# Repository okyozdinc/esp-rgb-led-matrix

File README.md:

# PIXELIX <!-- omit in toc -->

Full RGB LED matrix, based on an ESP32 and WS2812B LEDs.

- [Motivation](#motivation)
- [Overview](#overview)
  - [Original setup](#original-setup)
  - [Others](#others)
- [Installation](#installation)
- [Very First Startup](#very-first-startup)
  - [Variant 1: Configure wifi station SSID and passphrase with the browser](#variant-1-configure-wifi-station-ssid-and-passphrase-with-the-browser)
  - [Variant 2: Configure wifi station SSID and passphrase with the terminal](#variant-2-configure-wifi-station-ssid-and-passphrase-with-the-terminal)
  - [Pixelix Is Ready](#pixelix-is-ready)
- [User Interface](#user-interface)
- [Documentation](#documentation)
- [Used Libraries](#used-libraries)
- [FAQ](#faq)
  - [Where to change panel topology of the LED matrix?](#where-to-change-panel-topology-of-the-led-matrix)
  - [How to change text properties?](#how-to-change-text-properties)
  - [The display only shows a error code, like "E4". What does that mean?](#the-display-only-shows-a-error-code-like-e4-what-does-that-mean)
  - [How can I use animated icons?](#how-can-i-use-animated-icons)
  - [How do I know that my sensor is recognized?](#how-do-i-know-that-my-sensor-is-recognized)
  - [Why do I see sometimes values from the LDR in the SensorPlugin, although no LDR is installed?](#why-do-i-see-sometimes-values-from-the-ldr-in-the-sensorplugin-although-no-ldr-is-installed)
  - [How can I use alternative icons?](#how-can-i-use-alternative-icons)
  - [Is it possible to use a font with 8px height?](#is-it-possible-to-use-a-font-with-8px-height)
  - [How to configure the date/time format?](#how-to-configure-the-datetime-format)
- [Issues, Ideas And Bugs](#issues-ideas-and-bugs)
- [License](#license)
- [Contribution](#contribution)

# Motivation
I want to have a remote display to show multiple kind of information, running 24/7 reliable. Connected over wifi to the local network, it can be controlled via REST API or websocket.

| Some impressions |   |
| - | - |
|  |  |
|  |  |
|  | ... |

# Overview

The firmware contains a plugin concept (at compile time) to provide different functionalities. Each plugin can create its own layout and place the information as required. If you are only interested in showing just text provided via REST API, choose the JustTextPlugin. It uses the whole display size and will scroll text automatically. Sometimes in front of the text a nice icon is required, in this case choose the IconTextPlugin. These are only examples and you will find more in the [plugin list](./doc/PLUGINS.md).

A little bit more detail about the generic plugins and the first idea can be found in this [rough overview](./doc/Overview.pdf).

## Original setup
The original setup during development and the first release was:
* [ESP32 DevKitV1](https://github.com/playelek/pinout-doit-32devkitv1)
* WS2812B 5050 8x32 RGB Flexible LED Matrix Panel
* Power supply 5 V / 4 A

The following shows the absolute minimal wiring setup:

> :warning: **If you power all via USB**: Be very careful, because it may destroy your esp32 board if the LED current gets too high. Avoid increasing the LED display brightness or filling it complete with white pixels. Please use a external power supply with at least 5V / 4A.

## Others

In the meantime several other boards are supported as well. You can see them in the platformio configuration (platformio.ini) or the [list of boards](./doc/boards/README.md).

Additional supported variants, which were original not in focus:
* [LILYGO&reg; TTGO T-Display ESP32 WiFi and Bluetooth Module Development Board For Arduino 1.14 Inch LCD](http://www.lilygo.cn/prod_view.aspx?TypeId=50033&Id=1126&FId=t3:50033:3)
* [LILYGO&reg; T-Display ESP32-S3 1.9 inch ST7789 LCD Display Touch Screen Development Board](https://www.lilygo.cc/products/t-display-s3)

Although Pixelix was designed to show information, that is pushed or pulled via REST API, the following sensors can be directly connected and evaluated:
* Temperature and humidity sensors DHTx
* Temperature and humidity sensors SHT3x
* Digitial microphone INMP441 for some sound reactive stuff.

# Installation
The following steps are necessary for the first time and to get PIXELIX initial running on the target. Once it runs, later on the firmware and filesystem can be updated via the PIXELIX webinterface.

1. Setup the [toolchain](./doc/config/TOOLCHAIN-INSTALLATION.md).
2. [Build the software](./doc/config/SW-BUILD.md) and check whether the toolchain works.
3. [Upload/Update the software and firmware](./doc/config/SW-UPDATE.md) to the target.
4. Verify that the LED panel topology is correct and you see the "Hello World" on the display.

Note, that the LED panel topology and the display width/height can currently not be changed in the web interface. If its necessary, adapt first in ```./lib/HalLedMatrix/Board.h``` the _width_ and _height_ according your LED matrix. In the ```./lib/HalLedMatrix/LedMatrix.h``` file you have to change the member variable _m\_topo_ according to your physical panel topology. Take a look how your pixels are wired on the pcb and use the following page to choose the right one: https://github.com/Makuna/NeoPixelBus/wiki/Layout-objects

# Very First Startup
If the device starts the very first time, the wifi station SSID and passphrase settings are empty. They can be configured in two possible ways:
1. Using the browser and set them in the captive portal.
2. Using a terminal connecting via usb.

## Variant 1: Configure wifi station SSID and passphrase with the browser
Restart the device and keep the button pressed until it shows the SSID of the wifi access point, spawned by Pixelix. Search for it with your mobile device and connect.
* SSID: **pixelix**
* Passphrase: **Luke, I am your father.**

Depended on the type of device you are using for connecting to Pixelix, you may get a notification that further information is necessary and automatically routed to the captive portal. In any other case enter the URL http://192.168.4.1 in the browser address field.

Use the following default credentials to get access to the Pixelix webinterface:
* User: **luke**
* Password: **skywalker**

## Variant 2: Configure wifi station SSID and passphrase with the terminal
Connect Pixelix with your PC via usb and start a terminal. Use the following commands to set the wifi SSID and passphrase of your home wifi network:
* Write wifi passphrase: ```write wifi passphrase <your-passphrase>```
* Write wifi SSID: ```write wifi ssid <your-ssid>```
* Restart Pixelix: ```reset```

## Pixelix Is Ready
After configuration, restart again and voila, Pixelix will be available in your wifi network.

For changing whats displayed, go to its webinterface. Use the same credentials than for the captive portal in variant 1. In the "Display" page you can change it according to your needs.

# User Interface
* The user button provides several features:
    * On short pulse: Activates the next slot.
    * Two short pulses: Activates next fade effect.
    * Five short pulses: IP address is shown.
    * Long pressed: Increases the display brightness until maximum and then decreases until minimum. After that it will again increases it and so on.
* If the display's location is hard to reach, the virtual user button can be used. It is controllable via REST API and perfect for remote buttons like the [Shelly Button 1](https://shelly.cloud/products/shelly-button-1-smart-home-automation-device/).
* If a ambilight sensor (LDR) is connected, the display brightness is automatically adapted.
* The web interface provides the possibility to install plugins, control their duration in the slots and etc.
* Some plugin's spawn a dedicated REST API, see the web page of the plugin or have a look to the REST API documentation.

Note, the websocket interface is currently only used as a service in the web interface.

# Documentation
For more information, see the [documentation](./doc/README.md).

# Used Libraries
* [Arduino](https://github.com/platformio/platform-espressif32) - ESP32 Arduino framework - Apache-2.0 License
* [NeoPixelBus](https://github.com/Makuna/NeoPixelBus) - Controlling the LED matrix with hardware support (RMT) - LGPL-3.0 License
* [ESPAsyncWebServer](https://github.com/me-no-dev/ESPAsyncWebServer) - Webserver - LGPL-2.1 License
* [AsyncTCPSock](https://github.com/yubox-node-org/AsyncTCPSock) - TCP library, Reimplementation of the API of me-no-dev/AsyncTCP using high-level BSD sockets - LGPL-3.0 License
* [ArduinoJson](https://arduinojson.org/) - JSON handling - MIT License
* [StreamUtils](https://github.com/bblanchon/ArduinoStreamUtils) - Stream utilities - MIT License
* [Bootstrap](https://getbootstrap.com/) - CSS Framework - MIT License
* [POPPER JS](https://popper.js.org/) - POPPER JS - MIT License
* [jQuery](https://jquery.com/) - Javascript librariy for DOM handling - MIT License
* [Adafruit Unified Sensor Driver](https://github.com/adafruit/Adafruit_Sensor) - A unified sensor abstraction layer. - Apache License 2.0 License
* [Adafruit DHT sensor library](https://github.com/adafruit/DHT-sensor-library) - An Arduino library for the DHT series of low-cost temperature/humidity sensors. - MIT License
* [arduino-sht](https://github.com/Sensirion/arduino-sht) - An Arduino library for reading the SHT3x family of temperature and humidity sensors. - BSD-3-Clause License
* [TFT_eSPI](https://github.com/Bodmer/TFT_eSPI) - Arduino and PlatformIO IDE compatible TFT library optimised for the Raspberry Pi Pico (RP2040), STM32, ESP8266 and ESP32 that supports different driver chips - Mixed licenses: MIT, BSD, FreeBSD
* [arduinoFFT](https://github.com/kosme/arduinoFFT) - Fast Fourier Transform for Arduino. - GPL 3.0 License
* [mufonts](https://github.com/muwerk/mufonts) - A collection of fonts compatible with Adafruit GFX library. These fonts were developed when creating various samples for mupplet display code. - MIT License
* [JSZip](https://github.com/Stuk/jszip) - A library for creating, reading and editing .zip files with JavaScript, with a lovely and simple API. - MIT License
* [JSZipUtils](https://github.com/Stuk/jszip-utils) - A collection of cross-browser utilities to go along with JSZip. - MIT License
* [FileSaver.js](https://github.com/eligrey/FileSaver.js) - FileSaver.js is the solution to saving files on the client-side. - MIT License
* [Arduino client for MQTT](https://github.com/knolleary/pubsubclient) - This library provides a client for doing simple publish/subscribe messaging with a server that supports MQTT. - MIT License

# FAQ

## Where to change panel topology of the LED matrix?
First adapt in ```./lib/HalLedMatrix/Board.h``` the _width_ and _height_ according your LED matrix.

In the ```./lib/HalLedMatrix/LedMatrix.h``` file you have to change the member variable _m\_topo_ according to your physical panel topology. Take a look how your pixels are wired on the pcb and use the following page to choose the right one: https://github.com/Makuna/NeoPixelBus/wiki/Layout-objects

## How to change text properties?
Text properties can be changed using different keywords added to the string to be displayed.  
In order to be able to use these keywords, they must be prefixed by a backslash, otherwise they will only be treated as text.

The following keywords are available:
Keyword   | Description
----------|---------------------------------
\\#RRGGBB | Change text color (RRGGBB in hex)
\lalign   | Alignment left
\ralign   | Alignment right
\calign   | Alignment center

**Note**
- If theses keywords are used within the sourcecode they have to be prefixed with two backslashes (one additional for escaping).
- If these keywords are used via the [REST API](https://app.swaggerhub.com/apis/BlueAndi/Pixelix/1.2.0) all unsafe ASCII characters must be replaced by the respective percent encoding (see also [ASCII Encoding Reference](https://www.w3schools.com/tags/ref_urlencode.ASP)).
- The keywords can be combined.  

**Examples**

Sourcecode   | URL   | Result
----------|--------------------|-------------
\\\lalign\\\\#ff0000Hi! | %5Clalign%23ff0000Hi! | I<span style="color:red">Hi!</span>&nbsp;&nbsp;&nbsp;&nbsp;&nbsp;&nbsp;&nbsp;&nbsp;I
\\\calign\\#ff0000Hi! | %5Ccalign%23ff0000Hi! | I&nbsp;&nbsp;&nbsp;&nbsp;<span style="color:red">Hi!</span>&nbsp;&nbsp;&nbsp;&nbsp;I
\\\ralign\\#ff0000Hi! | %5Cralign%23ff0000Hi!| I&nbsp;&nbsp;&nbsp;&nbsp;&nbsp;&nbsp;&nbsp;&nbsp;<span style="color:red">Hi!</span>I

## The display only shows a error code, like "E4". What does that mean?

This is a low level error code. Please have a look into the following table.

| Error code | Description |
| ---------- | ----------- |
| E1 | Something happened, which can not be further explained, but was fatal. |
| E2 | There is a problem with the two-wire (i2c) interface. |
| E3 | There is no user button available. |
| E4 | Bad filesystem, did you explicit program the filesystem too? If not, please upload it. |
| E5 | The display manager didn't start up. |
| E6 | The system message handler didn't start up. |
| E7 | The update manager didn't start up. |

## How can I use animated icons?
Upload first the bitmap texture image (.bmp) and afterwards the sprite sheet file (.sprite). See the details [here](./doc/SPRITESHEET.md).

## How do I know that my sensor is recognized?

1. Check the log output from USB (not via web interface) right after startup (at this point WiFi is not connected yet).
2. Install the SensorPlugin and open the SensorPlugin website. There the sensor should be shown in the drop-down.

## Why do I see sometimes values from the LDR in the SensorPlugin, although no LDR is installed?

The LDR pin is configured as input (ADC) and it seems that the pin is floating, because there is the ext. pull-down missing.

## How can I use alternative icons?

Find details [here](./doc/ICONS.md).

## Is it possible to use a font with 8px height?
There are three font types defined:
* default (6px height)
* normal (6px height)
* large (8px height)

Note, the default font type is "normal".

The font type can be selected per plugin instance in the settings web page.

Example:
```json
{
    "name": "JustTextPlugin",
    "uid": 32690,
    "alias": "",
    "fontType": "large"
}
```

Not all plugin may support this in case they get conflicts with their layout.
If a plugin don't support it, it will use the default font type.

## How to configure the date/time format?
The date/time format used by plugins, e.g. the DateTimePlugin or the SunrisePlugin, can be configured in their configuration JSON file. Use the file editor in the web interface to modify it according to your needs. The file can be found in the ```/configuration``` folder and the filename is ```<PLUGIN-UID>.json```. The format specifiers following [strftime()](https://cplusplus.com/reference/ctime/strftime/).

Examples:
* ```%I:%M %p```: 02:30 PM
* ```%H:%M```: 14:30
* ```%m/%d```: 11/12
* ```%d.%m.```: 11.12.
* ```%d - %b```: 11 - Nov

You can colorize it by using the [text properties](#how-to-change-text-properties).

# Issues, Ideas And Bugs
If you have further ideas or you found some bugs, great! Create a [issue](https://github.com/BlueAndi/esp-rgb-led-matrix/issues) or if you are able and willing to fix it by yourself, clone the repository and create a pull request.

# License
The whole source code is published under the [MIT license](http://choosealicense.com/licenses/mit/).
Consider the different licenses of the used third party libraries too!

# Contribution
Unless you explicitly state otherwise, any contribution intentionally submitted for inclusion in the work by you, shall be licensed as above, without any
additional terms or conditions.

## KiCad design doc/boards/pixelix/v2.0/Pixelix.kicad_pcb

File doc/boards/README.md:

# PIXELIX <!-- omit in toc -->

# Boards <!-- omit in toc -->
Pixelix supports different ESP32 development boards. Own PCBs were developed too for easier assembling of e.g. the LED matrix, sensors, etc.

To find out which part shall be connected to which pin of your development board you can see in the following chapters.

- [Pixelix Board v1.5](#pixelix-board-v15)
- [Pixelix Board v2.0](#pixelix-board-v20)
- [Development Boards](#development-boards)
  - [DOIT ESP32 DEVKIT V1](#doit-esp32-devkit-v1)
  - [DOIT ESP32 DEVKIT V4](#doit-esp32-devkit-v4)
  - [ESP32 NodeMCU](#esp32-nodemcu)
  - [AZ-Delivery ESP-32 Dev Kit C V4](#az-delivery-esp-32-dev-kit-c-v4)
  - [LILYGO® TTGO ESP32 T-Display](#lilygo-ttgo-esp32-t-display)
  - [LILYGO® ESP32 T-Display S3](#lilygo-esp32-t-display-s3)

# Pixelix Board v1.5
This board was original developed with a ESP32 DevKit V1 development board as piggy bag.
* [Hardware description](./pixelix/v1.5/ELECTRONIC.md)
* [Bill of material](./pixelix/v1.5/BOM.md)
* [Pinning](../../lib/HalLedMatrix/Board.h)
* [Schematic](./pixelix/v1.5/schematics/)
* [PCB](./pixelix/v1.5/pcb/)
* [Housing Part 1](https://www.thingiverse.com/thing:2791276)
* [Housing Part 2](https://www.thingiverse.com/thing:3884621)

# Pixelix Board v2.0
The Pixelix board v2.0 is the successor of Pixelix board v1.5. It was designed for ESP32 DevKit V4 (4 MB flash) and the Adafruit ESP32 Feather V2 (8 MB flash) development board as piggy bag.
* [Hardware description](./pixelix/v2.0/ELECTRONIC.md)
* [Bill of material](./pixelix/v2.0/BOM.md)
* [Pinning](../../lib/HalLedMatrix/Board.h)
* [Housing](./pixelix/v2.0/3D-files/)

# Development Boards

## DOIT ESP32 DEVKIT V1
* [Pinning](../../lib/HalLedMatrix/Board.h) (equal to Pixelix boards)

## DOIT ESP32 DEVKIT V4
* [Pinning](../../lib/HalLedMatrix/Board.h) (equal to Pixelix boards)

## ESP32 NodeMCU
* [Pinning](../../lib/HalLedMatrix/Board.h) (equal to Pixelix boards)

## AZ-Delivery ESP-32 Dev Kit C V4
* Manufacturer: [AZ-Delivery](https://www.az-delivery.de/products/esp-32-dev-kit-c-v4)
* [Pinning](../../lib/HalLedMatrix/Board.h) (equal to Pixelix boards)

## LILYGO&reg; TTGO ESP32 T-Display
The LILYGO&reg; TTGO ESP32 T-Display development board is handled separately, because the onboard display is used instead of a external LED matrix.

* Manufacturer: [Lilygo](http://www.lilygo.cn/prod_view.aspx?TypeId=50033&Id=1126&FId=t3:50033:3)
* [Pinning](../../lib/HalTftDisplay/Board.h)

## LILYGO&reg; ESP32 T-Display S3
The LILYGO&reg; ESP32 T-Display S3 development board is handled separately, because the onboard display is used instead of a external LED matrix.

* Manufacturer: [Lilygo](https://www.lilygo.cc/products/t-display-s3)
* [Pinning](../../lib/HalTftDisplay/Board.h)

# Issues, Ideas And Bugs <!-- omit in toc -->
If you have further ideas or you found some bugs, great! Create a [issue](https://github.com/BlueAndi/esp-rgb-led-matrix/issues) or if you are able and willing to fix it by yourself, clone the repository and create a pull request.

# License <!-- omit in toc -->
The whole source code is published under the [MIT license](http://choosealicense.com/licenses/mit/).
Consider the different licenses of the used third party libraries too!

# Contribution <!-- omit in toc -->
Unless you explicitly state otherwise, any contribution intentionally submitted for inclusion in the work by you, shall be licensed as above, without any
additional terms or conditions.

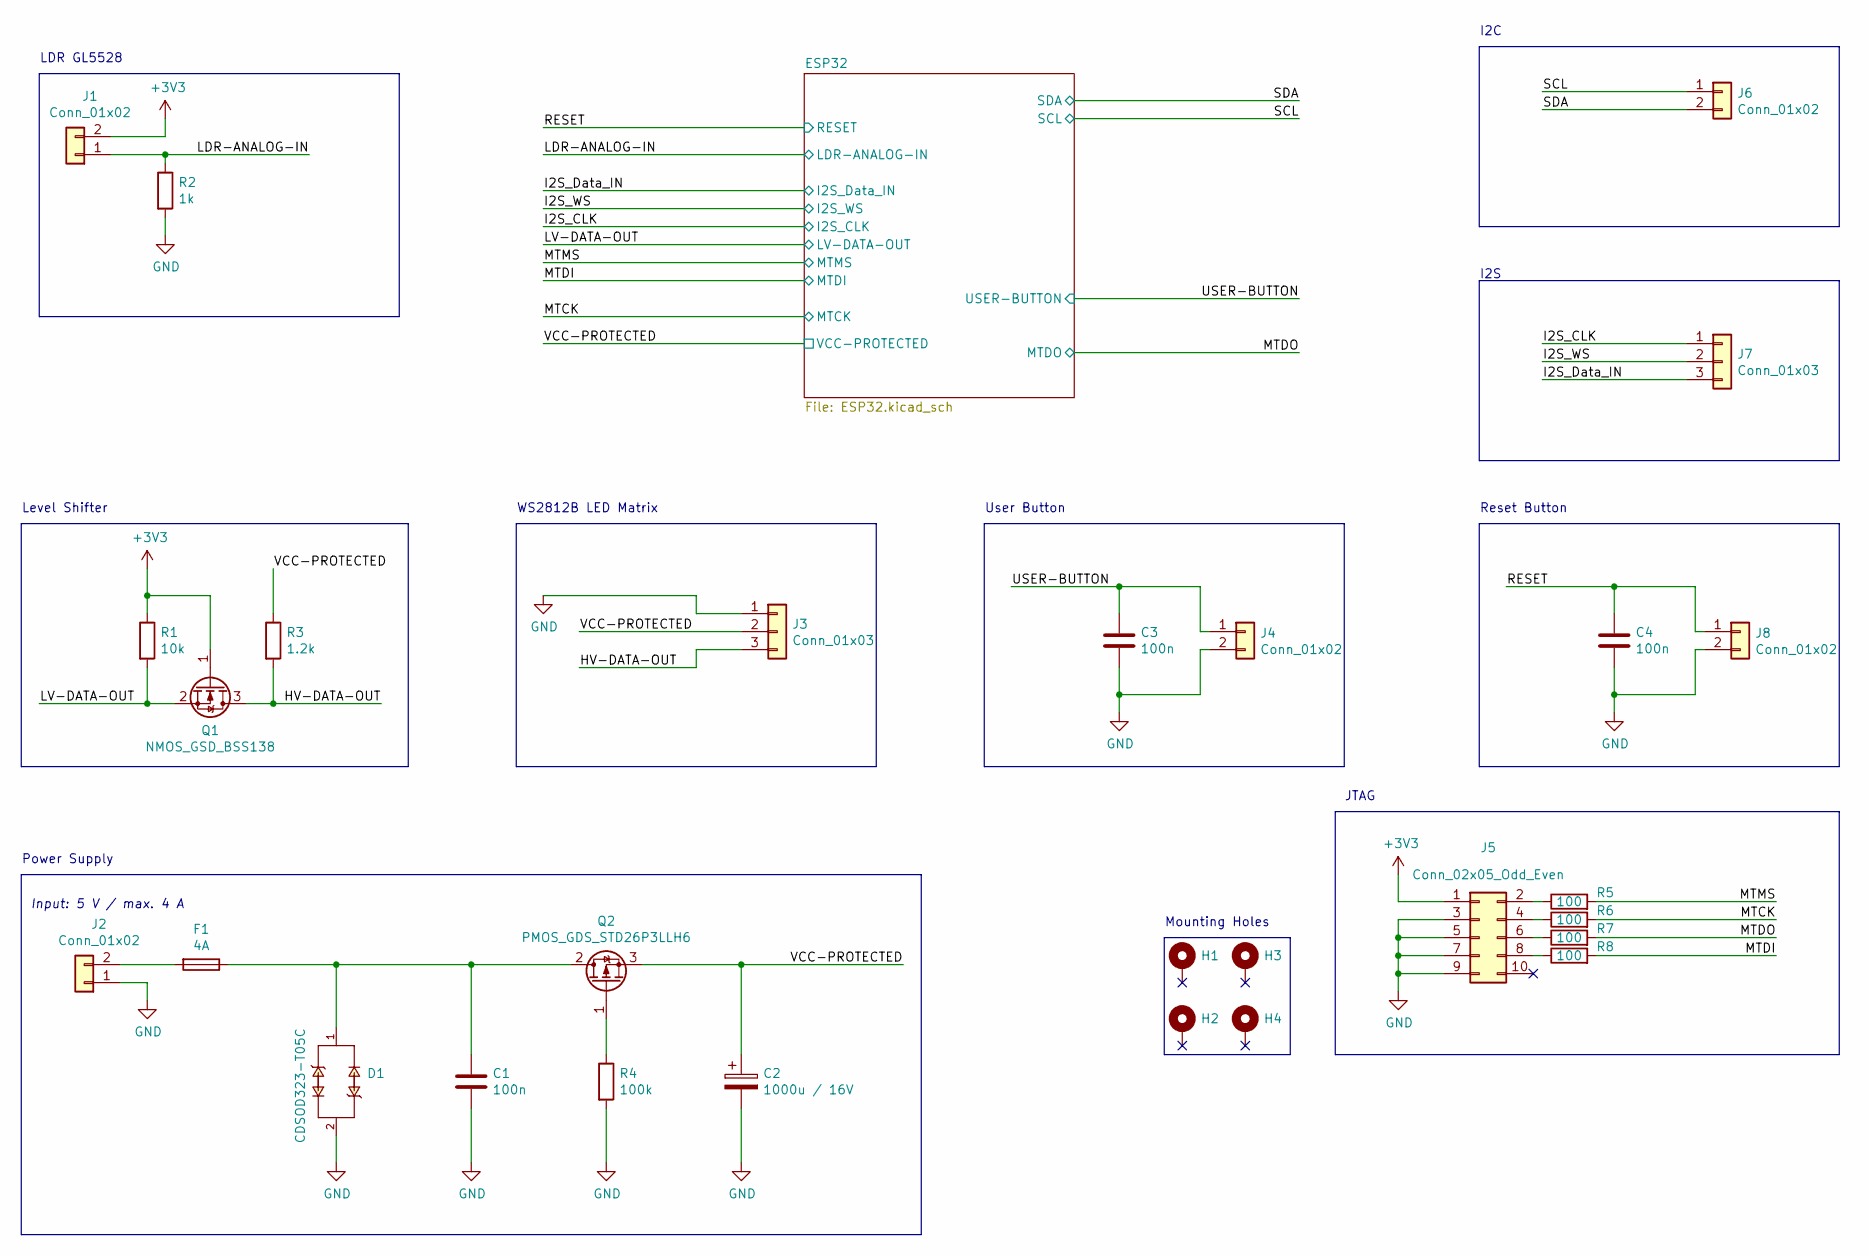
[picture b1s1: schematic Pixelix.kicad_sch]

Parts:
C1, C3, C4: 100n; C_1206_3216Metric_Pad1.33x1.80mm_HandSolder; Part-No. X7R1206B100N
C2: 1000u / 16V; CP_Radial_D8.0mm_P3.50mm_horizontal; Part-No. EEU-FR1C102L
D1: CDSOD323-T05C; Part-No. CDSOD323-T05C
F1: 4A; FUSE_0154004.DR; Part-No. 0154004.DRT
H1, H2, H3, H4: MountingHole_Pad; MountingHole_2.2mm_M2_Pad_Via
J1, J2, J4, J6, J8: Conn_01x02; 66200211022; Part-No. 66200211022
J3, J7: Conn_01x03; 66200311022; Part-No. 66200311022
J5: Conn_02x05_Odd_Even; 61201021621; Part-No. 61201021621
Q1: NMOS_GSD_BSS138; SOT-23_Handsoldering; Part-No. BSS138
Q2: PMOS_GDS_STD26P3LLH6; TO-252-3_TabPin2; Part-No. STD26P3LLH6
R1: 10k; R_1206_3216Metric_Pad1.30x1.75mm_HandSolder; Part-No. RC1206JR-0710KL
R2: 1k; R_1206_3216Metric_Pad1.30x1.75mm_HandSolder; Part-No. RC1206JR-071KL
R3: 1.2k; R_1206_3216Metric_Pad1.30x1.75mm_HandSolder; Part-No. RC1206JR-071K2L
R4: 100k; R_1206_3216Metric_Pad1.30x1.75mm_HandSolder; Part-No. RK73H2BTTD14
R5, R6, R7, R8: 100; R_1206_3216Metric_Pad1.30x1.75mm_HandSolder; Part-No. RC1206JR-07100RL

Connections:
+3V3: J1.2, J5.1, Q1.1 (G), R1.1; also elsewhere on the board
/HV-DATA-OUT: J3.3, Q1.3 (D), R3.2
/I2S_CLK: J7.1; also elsewhere on the board
/I2S_Data_IN: J7.3; also elsewhere on the board
/I2S_WS: J7.2; also elsewhere on the board
/LDR-ANALOG-IN: J1.1, R2.1; also elsewhere on the board
/LV-DATA-OUT: Q1.2 (S), R1.2; also elsewhere on the board
/MTCK: R6.2; also elsewhere on the board
/MTDI: R8.2; also elsewhere on the board
/MTDO: R7.2; also elsewhere on the board
/MTMS: R5.2; also elsewhere on the board
/RESET: C4.1, J8.1; also elsewhere on the board
/SCL: J6.1; also elsewhere on the board
/SDA: J6.2; also elsewhere on the board
/USER-BUTTON: C3.1, J4.1; also elsewhere on the board
/VCC-PROTECTED: C2.1, J3.2, Q2.3 (S), R3.1; also elsewhere on the board
GND: C1.2, C2.2, C3.2, C4.2, D1.2, J2.1, J3.1, J4.2, J5.3, J5.5, J5.7, J5.9, J8.2, R2.2, R4.2; also elsewhere on the board
unnamed: C1.1, D1.1, F1.1, Q2.2 (D)
unnamed: F1.2, J2.2
unnamed: J5.2, R5.1
unnamed: J5.4, R6.1
unnamed: J5.6, R7.1
unnamed: J5.8, R8.1
unnamed: Q2.1 (G), R4.1

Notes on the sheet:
User Button
LDR GL5528
WS2812B LED Matrix
I2S
JTAG
I2C
Power Supply
Mounting Holes
Input: 5 V / max. 4 A
Level Shifter
Reset Button

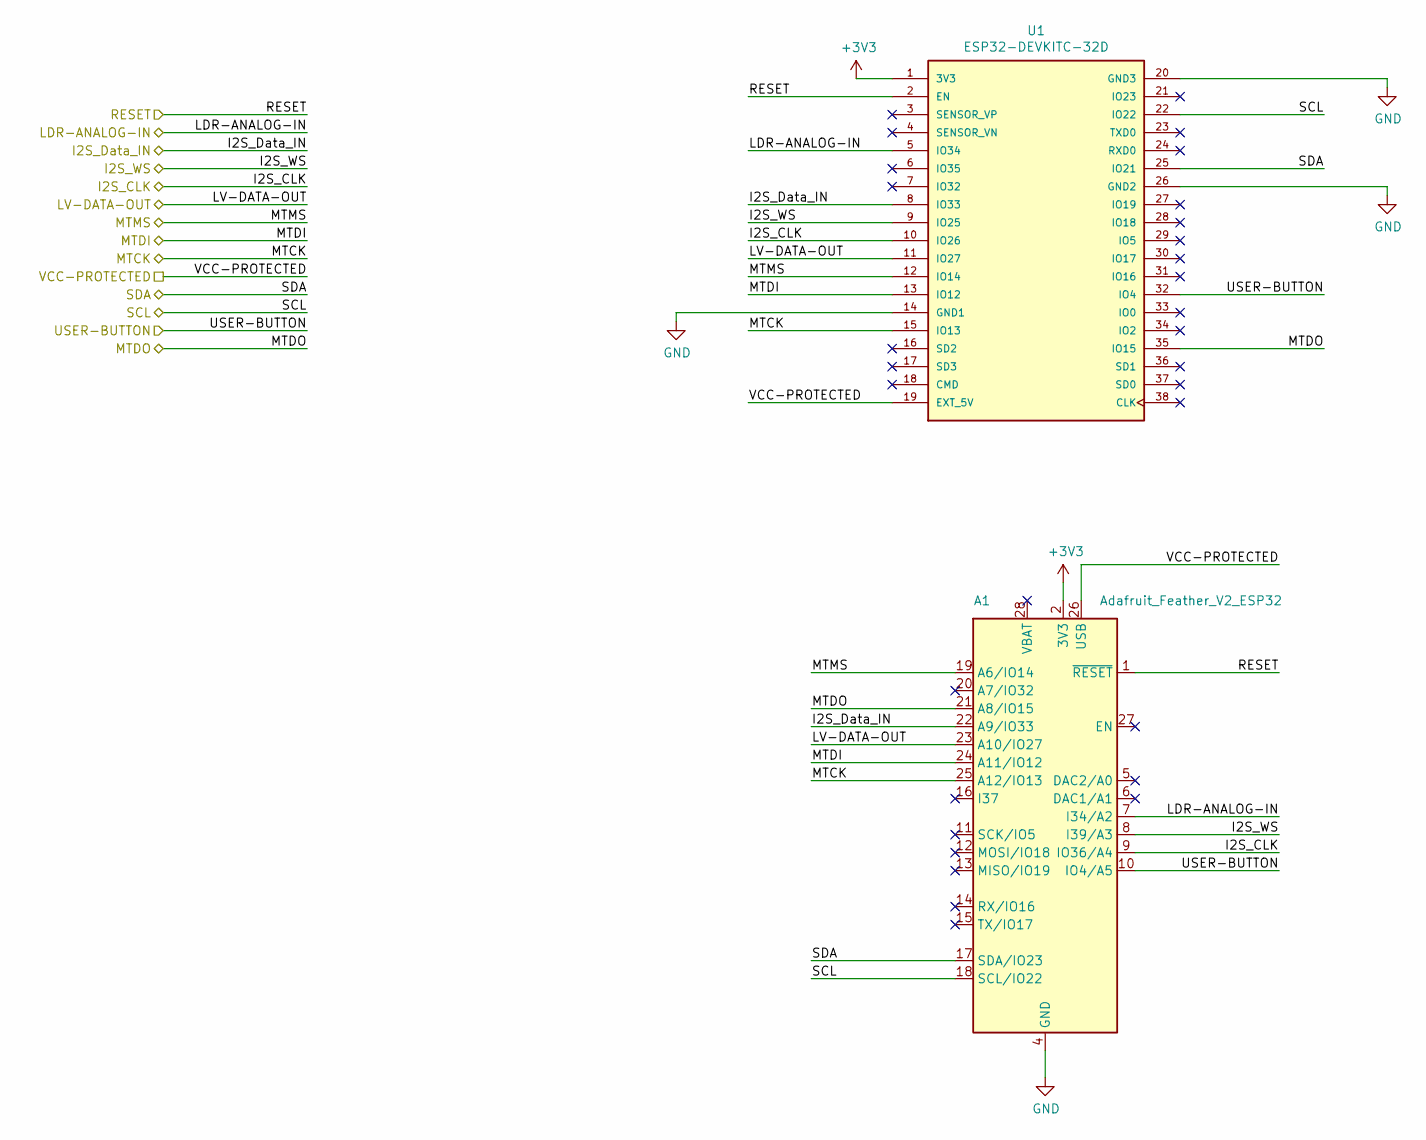
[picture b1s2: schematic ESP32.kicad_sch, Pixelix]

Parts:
A1: Adafruit_Feather_V2_ESP32; Part-No. Feather V2
U1: ESP32-DEVKITC-32D; MODULE_ESP32-DEVKITC-32D; Part-No. ESP32-DEVKITC-32D

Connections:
+3V3: A1.2 (3V3), U1.1 (3V3); also elsewhere on the board
/I2S_CLK: A1.9 (IO36/A4), U1.10 (IO26); also elsewhere on the board
/I2S_Data_IN: A1.22 (A9/IO33), U1.8 (IO33); also elsewhere on the board
/I2S_WS: A1.8 (I39/A3), U1.9 (IO25); also elsewhere on the board
/LDR-ANALOG-IN: A1.7 (I34/A2), U1.5 (IO34); also elsewhere on the board
/LV-DATA-OUT: A1.23 (A10/IO27), U1.11 (IO27); also elsewhere on the board
/MTCK: A1.25 (A12/IO13), U1.15 (IO13); also elsewhere on the board
/MTDI: A1.24 (A11/IO12), U1.13 (IO12); also elsewhere on the board
/MTDO: A1.21 (A8/IO15), U1.35 (IO15); also elsewhere on the board
/MTMS: A1.19 (A6/IO14), U1.12 (IO14); also elsewhere on the board
/RESET: A1.1 (~RESET), U1.2 (EN); also elsewhere on the board
/SCL: A1.18 (SCL/IO22), U1.22 (IO22); also elsewhere on the board
/SDA: A1.17 (SDA/IO23), U1.25 (IO21); also elsewhere on the board
/USER-BUTTON: A1.10 (IO4/A5), U1.32 (IO4); also elsewhere on the board
/VCC-PROTECTED: A1.26 (USB), U1.19 (EXT_5V); also elsewhere on the board
GND: A1.4 (GND), U1.14 (GND1), U1.20 (GND3), U1.26 (GND2); also elsewhere on the board

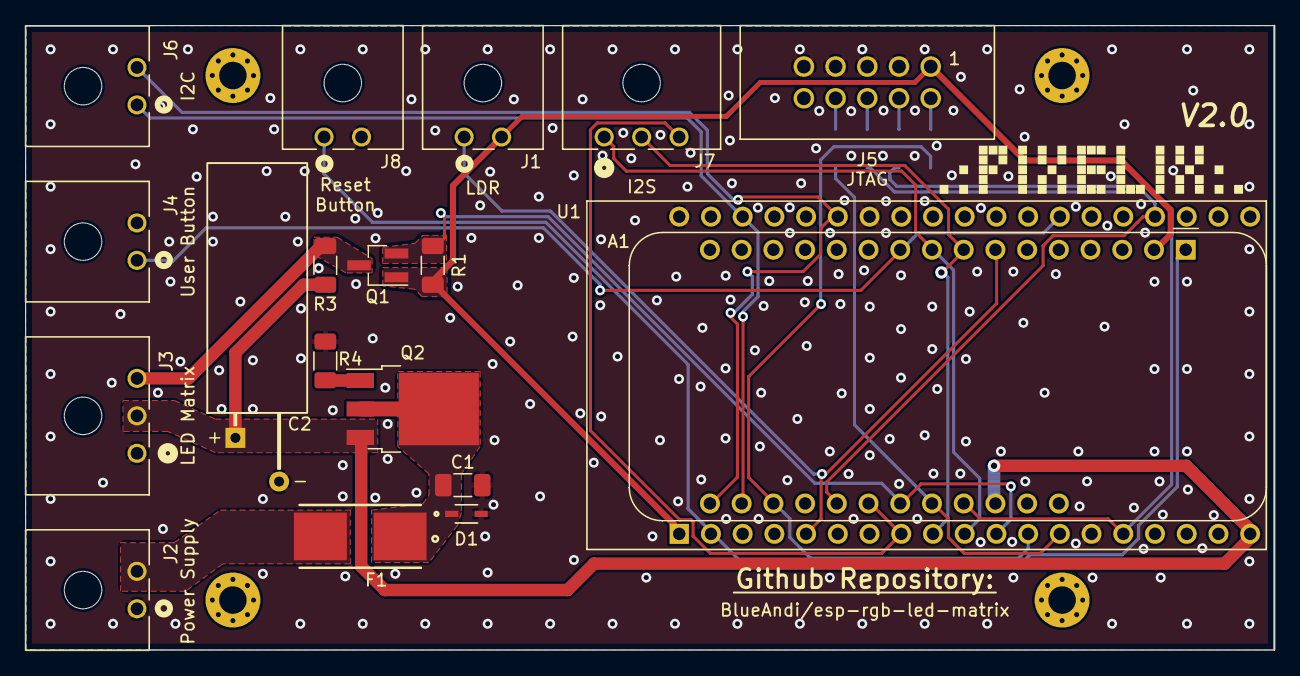
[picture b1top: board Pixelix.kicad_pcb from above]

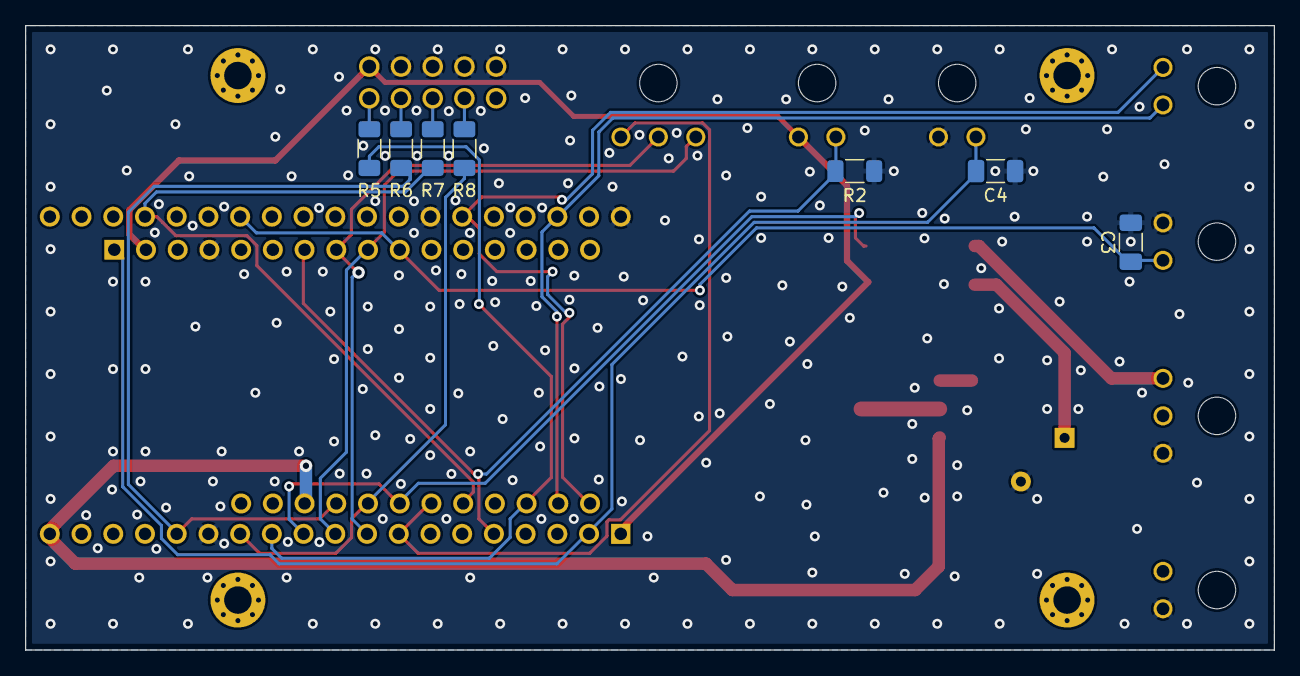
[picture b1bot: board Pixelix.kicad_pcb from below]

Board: 2 copper layers, 100.0 x 50.0 mm, 30 parts (7 on the bottom side), 24 nets.

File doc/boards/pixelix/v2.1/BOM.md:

# PIXELIX
![PIXELIX](../../../images/LogoBlack.png)

[![License](https://img.shields.io/badge/license-MIT-blue.svg)](http://c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

# BOM

| Amount | Description | Package | Part | URL |
| --- | --- | --- | --- | --- |
| 1 | Adafruit Feather V2 | Feather V2 | A1 | [Adafruit](https://www.adafruit.com/product/5400), [Amazon](https://www.amazon.de/-/en/Adafruit-ESP32-Feather-V2-8MB-Fla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, [Mouser](https://www.mouser.de/ProductDetail/Adafruit/5400?qs=MyNHzdo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 |
| 3 | Capacitor 100 nF | C1206 | C1, C3, C4 | [Reichelt](https://www.reichelt.de/vielschicht-kerko-100nf-50v-125-c-ke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, [Mouser](https://www.mouser.de/ProductDetail/KEMET/C1206C104K5RACTM?q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 |
| 1 | Capacitor 1000 uF / 16 V | E5-8.5 | C2 | [Reichelt](https://www.reichelt.de/elko-radial-1-0-mf-16-v-105-c-low-es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, [Mouser](https://www.mouser.de/ProductDetail/Panasonic/EEU-FR1C102L?q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 |
| 4 | Resistor 100 Ohm | R1206 | R5, R6, R7, R8 | [Reichelt](https://www.reichelt.de/smd-widerstand-1206-100-ohm-250-mw-5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, [Mouser](https://www.mouser.de/ProductDetail/YAGEO/RC1206JR-07100RL?q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 |
| 1 | Resistor 1 kOhm | R1206 | R2 | [Reichelt](https://www.reichelt.de/smd-widerstand-1206-1-0-kohm-250-mw-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, [Mouser](https://www.mouser.de/ProductDetail/YAGEO/RC1206JR-071KL?qs=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  |
| 1 | Resistor 1.2 kOhm | R1206 | R3 | [Reichelt](https://www.reichelt.de/smd-widerstand-1206-1-2-kohm-250-mw-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, [Mouser](https://www.mouser.de/ProductDetail/YAGEO/RC1206JR-071K2L?qs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  |
| 1 | Resistor 10 kOhm | R1206 | R1 | [Reichelt](https://www.reichelt.de/smd-widerstand-1206-10-kohm-250-mw-5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, [Mouser](https://www.mouser.de/ProductDetail/YAGEO/RC1206JR-0710KL?qs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 |
| 1 | Resistor 100 kOhm | R1206 | R4 | [Reichelt](https://www.reichelt.de/smd-widerstand-1206-100-kohm-250-mw-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, [Mouser](https://www.mouser.de/ProductDetail/YAGEO/RC1206FR-07100KL?q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 |
| 1 | ESD suppressor CDSOD323-T05C | SOD-323 | D1 | [Conrad](https://www.conrad.de/de/p/bourns-tvs-diode-cdsod323-t05c-so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, [Farnell](https://de.farnell.com/bourns/cdsod323-t05c/tvs-diode-bidir-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, [Mouser](https://www.mouser.de/ProductDetail/Bourns/CDSOD323-T05C?qs=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 |
| 1 | Micro fuse block, 4A slow | OMNI-BLOK | F1 | [Reichelt](https://www.reichelt.de/smd-sicherungshalter-mit-sicherung-4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, [Farnell](https://de.farnell.com/littelfuse/0154004-drt/sicherung-smd-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, [Mouser](https://www.mouser.de/ProductDetail/?qs=gu7KAQ731UQeedYeniUN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 |
| 1 | Espressif ESP32-DEVKIT | ESP32-DEVKITC-32D | U1 | [Mouser](https://www.mouser.de/ProductDetail/Espressif-Systems/ESP32-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, [Amazon](https://www.amazon.de/s?k=ESP32-DEVKITC-32D&i=computers&__mk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 |
| 1 | N-channel mosfet BSS138 | SOT23 | Q1 | [Reichelt](https://www.reichelt.de/mosfet-n-ch-50v-0-22a-0-36w-sot-23-b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, [Farnell](https://de.farnell.com/on-semiconductor/bss138/mosfet-n-kana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, [Mouser](https://www.mouser.de/ProductDetail/onsemi-Fairchild/BSS138?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 |
| 1 | P-channel mosfet STD26P3LLH6 | TO252 | Q2 | [Reichelt](https://www.reichelt.de/mosfet-p-ch-30v-12a-0-03r-to252-std2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, [Farnell](https://de.farnell.com/stmicroelectronics/std26p3llh6/mosfet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, [Mouser](https://www.mouser.de/ProductDetail/STMicroelectronics/STD26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 |
| 5 | Conn_01x02 | Wuerth Elektronik 66200211022 | J1, J2, J4, J6, J8 | [Farnell](https://de.farnell.com/wurth-elektronik/66200211022/steckv-s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, [Mouser](https://www.mouser.de/c/?q=66200211022) |
| 2 | Conn_01x03 | Wuerth Elektronik 66200311022 | J3, J7 | [Farnell](https://de.farnell.com/wurth-elektronik/66200311022/stiftlei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, [Mouser](https://www.mouser.de/ProductDetail/Wurth-Elektronik/6620031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 |
| 1 | Conn_02x05_Odd_Even | Wuerth Elektronik 61201021621 | J5 | [Farnell](https://de.farnell.com/wurth-elektronik/61201021621/stiftlei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, [Mouser](https://www.mouser.de/ProductDetail/Wurth-Elektronik/6120102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 |
| --- | --- | --- | --- | --- |
| 5 | Plug_01x02 | Wuerth Elektronik 662002013322 | J1*, J2*, J4*, J6*, J8* | [Mouser](https://www.mouser.de/ProductDetail/Wurth-Elektronik/6620020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 |
| 2 | Plug_01x03 | Wuerth Elektronik 662003013322 | J3*, J7* | [Mouser](https://www.mouser.de/ProductDetail/Wurth-Elektronik/6620030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 |
| 1 | WS2812B 5050 8x32 RGB Flexible LED Panel Matrix | - | - | [Amazon](https://www.amazon.de/CHINLY-Flexible-Individuellement-adres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 |
| 1 | Power supply 5 V / 5 A (4 A would be enough) | - | - | [Reichelt](https://www.reichelt.de/tischnetzteil-25-w-5-v-5-a-mw-gst40a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, [Mouser](https://www.mouser.de/ProductDetail/CUI-Inc/SDM36-5-U-P5?qs=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 |
| 1 | Power cable | - | - | [Reichelt](https://www.reichelt.de/netzkabel-schutzkontaktstecker-gew-1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, [Mouser](https://www.mouser.de/ProductDetail/Qualtek/364002-D01?qs=HF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 |
| 1 | Power supply plug | - | - | [Mouser](https://www.mouser.de/ProductDetail/CUI-Devices/PJ-065A?qs=W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 |
| 1 | USER-Button | - | - | [Amazon](https://www.amazon.de/-/en/gp/product/B08L49F7DV) |
| 1 | RESET-Button | - | - | [Amazon](https://www.amazon.de/-/en/gp/product/B08YMZGLWX) |
| 1 | Light Sensor  | LDR5528  | - | [Amazon](https://www.amazon.de/-/en/AZDelivery-pieces-resistor-diodes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 |
| 1 | Audio Sensor-Module | INMP441  | - | [Amazon](https://www.amazon.de/-/en/gp/product/B09JFDJ9BF) |
| 4 | Insert-Nuts M2 | - | - | [Amazon](https://www.amazon.de/ruthex-Gewindeeinsatz-St%C3%BCck-Gewin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

* Note, only **ONE** ESP32 is required. Either U1 or A1.
* Note, you can also use the *Molex 2157601002* connectors for J1, J2, J4, J6 and J8 and the *Molex 2157601003* for J3 and J7.
* Note, you can also use the *Molex 2157591002* plugs for J1*, J2*, J4*, J6* and J8* and the *Molex 2157591003* for J3* and J7*. You also need crimp terminals (e.g. *Wuerth Elektronik 66200113722DEC* or *Molex 2064600021*)
* Do **NOT** combine connectors and plugs from Molex and Wuerth Elektronik!

# Issues, Ideas And Bugs
If you have further ideas or you found some bugs, great! Create a [issue](https://github.com/BlueAndi/esp-rgb-led-matrix/issues) or if you are able and willing to fix it by yourself, clone the repository and create a pull request.

# License
The whole source code is published under the [MIT license](http://choosealicense.com/licenses/mit/).

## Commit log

2020-11-16 The LED matrix layout can now be configured during runtime. Note, if the corresponding setting is changed via web interface, a reboot is necessary.
2023-03-29 Renormalized Line Endings
2023-05-24 check_src_filters

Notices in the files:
doc/boards/pixelix/v2.1/BOM.md:
[License](https://img.shields.io/badge/license-MIT-blue.svg)](http://choosealicense.com/licenses/mit/)
